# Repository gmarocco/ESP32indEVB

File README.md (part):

# ESP32-S3 Industrial Development Board — rev. 3

An ESP32-S3 development board with industrial-style I/O: an **isolated CAN bus** port, an **isolated RS-485** port, a **relay output**, two **0–30 V analog inputs**, **nine ESD-protected GPIOs**, a **3 × 3 RGB LED matrix** and a **prototyping area**. It runs from a **7–36 V DC** supply or from either of its two USB-C ports. Everything fits on a 99 × 94 mm four-layer PCB designed in KiCad 10.

## Features

- **Espressif ESP32-S3FN8**: dual-core Xtensa LX7 MCU, 2.4 GHz Wi-Fi and Bluetooth LE, 8 MB in-package flash, on-board chip antenna
- **Two USB-C ports**:
  - **debug USB**: FTDI FT230X USB-to-UART bridge on UART0
  - **native USB**: ESP32-S3 USB Serial/JTAG and USB OTG
- **Isolated CAN bus** (ESP32-S3 TWAI controller): Microchip MCP2562 transceiver, 120 Ω termination
- **Isolated RS-485**: MAX13488E half-duplex transceiver with automatic direction control, 120 Ω termination and fail-safe bias
- **Galvanic isolation** for both buses: ADuM3201 digital isolators and a Traco TEA 1-0505 isolated DC/DC converter
- **3 × 3 WS2812B RGB LED matrix** with a 3.3 V → 5 V level shifter on the data line
- **SPDT relay** (Finder 34.51, 6 A contacts) on a screw terminal block
- **Two analog inputs, 0–30 V**: resistor divider and op-amp buffer for each input
- **Nine ESD-protected GPIOs** on three 2.54 mm headers, with fused 3.3 V and 5 V outputs
- **Header for an SSD1306 I²C OLED display**
- **Wide-range supply**: 7–36 V DC input with reverse-polarity, overcurrent and transient protection, switching regulator to 5 V
- **Prototyping area** with through-hole pads and footprints for SOIC-8, MSOP-8 and SOT-23-5 parts
- **Reset, boot and user push buttons**, user LED, potentiometer on an ADC input
- **JTAG test points** and stitching vias along the board perimeter

## Block diagram

Power tree:

```mermaid
flowchart LR
    VIN["DC input 7-36 V (EXT_POWER1)"] --> PROT["F2 PTC + D4 TVS + D5 reverse-polarity diode"]
    PROT --> DCDC["TSR 1-2450 5 V regulator (PS1)"]
    DCDC -- "D6" --> OR["+5V_PRO (diode OR)"]
    USBD["Debug USB-C VBUS"] -- "D12" --> OR
    USBN["Native USB-C VBUS"] -- "D13" --> OR
    OR --> P5["+5V (F1 PTC + L5 LC filter)"]
    P5 --> LDO["NCP1117 3.3 V LDO (U1)"] --> P33["+3V3"]
    P5 --> ISO["TEA 1-0505 isolated DC/DC (PS2)"] --> P5ISO["+5V_ISO for CAN and RS-485"]
    P5 --> LEDS["WS2812B matrix, relay coil"]
    P5 -- "F3 0.5 A" --> O5["+5V_OUT (J7)"]
    P33 -- "F5 0.5 A" --> O33["+3V3_OUT (J6)"]
```

## Circuit description

The full schematic is available as a PDF file: [ESP32_ind_EVB_V3_schematic.pdf](production/ESP32_ind_EVB_V3_schematic.pdf)

| Sheet | File | Content |
|---|---|---|
| Root | `ESP32_ind_EVB_V3.kicad_sch` | Block diagram |
| gerarchico | `gerarchico.kicad_sch` | Hierarchy sheet that links the sub-sheets below |
| Power | `power.kicad_sch` | DC input, protection, 5 V switching regulator, 3.3 V LDO, fused header supplies |
| ESP32-S3 MCU | `mcu_sch.kicad_sch` | ESP32-S3, crystals, antenna, SPI flash, native USB-C, buttons, OLED header |
| bus | `bus_sch.kicad_sch` | Debug USB-C and FT230X, isolated CAN bus and RS-485, isolated DC/DC |
| GPIO | `GPIO_sch.kicad_sch` | Protected GPIO headers, analog inputs, relay, potentiometer |
| LED_MATRIX_WS2812B | `LED_MATRIX_WS2812B.kicad_sch` | 3 × 3 WS2812B matrix and level shifter |
| breadboard | `breadboard_sch.kicad_sch` | Prototyping area |

### Power supply (Power sheet)

The board has three power sources. Schottky diodes (Comchip CDBA340, 40 V / 3 A) combine them on the `+5V_PRO` node, so any of them can power the board:

| Source | Path to `+5V_PRO` |
|---|---|
| DC input `EXT_POWER1`, 7–36 V | **F2** (PTC, 1.5 A hold) → **D4** (SMBJ36CA bidirectional TVS) → **D5** (reverse-polarity diode) → **PS1** (Traco TSR 1-2450, 5 V / 1 A switching regulator) → **D6** |
| Debug USB-C (`USBC_FTDI1`) | VBUS → **D12** |
| Native USB-C (`USBC_ESP32`) | VBUS → **D13**. R40 (0 Ω, not fitted) can bypass the diode |

From `+5V_PRO`:

- **F1** (PTC, 1.5 A hold) and an LC filter (**L5**, Murata 4.7 µH, with C41 and C6) make the **+5V** rail. It feeds the LED matrix, the relay coil, the isolated DC/DC converter and the 5 V header pin.
- **U1** (onsemi NCP1117, 3.3 V LDO) makes the **+3V3** rail from +5V through **R33** (0 Ω, 0.5 W). Remove R33 to isolate the 3.3 V loads or to measure their current.
- Two ferrite beads (BLM18AG102) separate the analog supplies:
  - L1 feeds **+3.3VA** (op-amp and potentiometer).
  - L2 feeds the ESP32-S3 `VDDA` pins.
- The header supply pins are protected by 0.5 A PTC fuses and TVS diodes:
  - `+5V_OUT`: F3 and D27 (SMBJ5.0A)
  - `+3V3_OUT`: F5 and D28 (SMBJ3V3)
- **D14** shows that the 3.3 V rail is on.

> **Note:** when the board runs from USB, the +5V rail is one Schottky diode drop below VBUS.

### ESP32-S3 microcontroller (ESP32-S3 MCU sheet)

- **IC10** is an **Espressif ESP32-S3FN8** with 8 MB of in-package flash.
- **Clocks**:
  - **Y1** (Diodes FL4000157Z) is the 40 MHz main crystal, with C11 and C12 (20 pF).
  - **Y2** (Abracon ABS07AIG) is the 32.768 kHz RTC crystal on GPIO15/GPIO16, with C13 and C14 (30 pF).
- **Antenna**: **ANT1** (Walsin RFANT3216120A5T) is a 2.4 GHz chip antenna. A π matching network sits between it and the `LNA_IN` pin: L3 (2.4 nH), C48 and C49 (1.8 pF). C15 and L4 are not fitted.
- **Reset**: **S3** pulls `CHIP_PU` low. R3 and R42 (100 kΩ) pull it up, and C5 (1 µF) delays the start-up after power-on.
- **Boot and user buttons**:
  - **S4** (BOOT) is on GPIO0.
  - **S2** (user button) is on GPIO2, with a 100 kΩ pull-up (R9) and a 100 nF debounce capacitor (C20).
- **User LED**: **D15** with a 470 Ω resistor (R25). See [Known issues](#known-issues-rev-3) for its GPIO.
- **External SPI flash**: **U2** (Winbond W25Q80DV, 8 Mbit) is connected to the SPI flash bus through the 0 Ω links R2, R6, R7, R10 and R11.
- **Native USB**:
  - The USB-C receptacle **USBC_ESP32** connects to GPIO19 (D−) and GPIO20 (D+) through **IC1** (ST USBLC6-2SC6 ESD protection).
  - R12 and R14 (5.1 kΩ) pull CC1 and CC2 down, so the board is seen as a USB device.
  - The connector shield goes to GND through R13 (1 MΩ) in parallel with C21 (3.3 nF / 1 kV).
  - Header **J1** (+5V, D−, D+, GND) carries the same port, through R43/R44 (0 Ω), for a panel-mount USB connector.
- **I²C**: GPIO5 (SCL) and GPIO6 (SDA) go through 0 Ω links (R63, R64) and have 1.5 kΩ pull-ups (R67, R68). The 4-pin header **LCD1** (GND, 3V3, SCL, SDA) accepts an SSD1306 OLED module.

### USB debug port (bus sheet)

- **IC7** (FTDI **FT230XS**) is a USB-to-UART bridge connected to the ESP32-S3 UART0 through R52/R53 (0 Ω):
  - FT230X `TXD` → GPIO44 (`U0RXD`)
  - FT230X `RXD` ← GPIO43 (`U0TXD`)
- It runs from the VBUS of its own USB-C port (**USBC_FTDI1**), and its internal 3.3 V regulator sets the I/O level.
- **IC4** (USBLC6-2SC6) protects the data lines. R17 and R18 (5.1 kΩ) pull CC1 and CC2 down. The shield goes to GND through R19 (1 MΩ) in parallel with C24 (3.3 nF / 1 kV).
- **D7** and **D8** are the serial activity LEDs, driven by the FT230X `CBUS2` and `CBUS1` pins.
- Header **J4** (GND, D+, D−, VBUS) carries the same port for a panel-mount USB connector.
- The FT230X `RTS#` and `CTS#` lines are not connected, so there is no automatic reset into the bootloader. Use the BOOT button (see [Programming](#programming)).

### Isolated CAN bus and RS-485 (bus sheet)

Both buses sit in a common isolated domain:

- **PS2** (Traco TEA 1-0505) is a 1 W isolated DC/DC converter. It makes `+5V_ISO` / `GND_ISO` from +5V.
- **IC2** (CAN) and **IC3** (RS-485) are Analog Devices **ADuM3201** dual-channel digital isolators. Their MCU side runs from +3V3 and their bus side from `+5V_ISO`.
- CAN and RS-485 share the same `GND_ISO`. They are isolated from the MCU, but not from each other.

| | **CAN bus** | **RS-485** |
|---|---|---|
| MCU pins | GPIO37 TX, GPIO38 RX (TWAI controller), through R57/R56 (0 Ω) | GPIO17 TX, GPIO18 RX (UART1), through R54/R55 (0 Ω) |
| Isolator | IC2 | IC3 |
| Transceiver | **IC5**, Microchip MCP2562. `STBY` is tied low through R21, so it is always active | **IC6**, MAX13488E, half-duplex with AutoDirection: no direction pin is needed |
| Termination | R29, 120 Ω (fitted) | R28, 120 Ω (fitted) |
| Fail-safe bias | – | R22 / R23 (1 kΩ) on A / B |
| Common-mode choke | FL1, TDK ACT45B-101-2P | FL2, TDK ACT45B-101-2P |
| ESD protection | D9, Nexperia PESD2CANFD27L | D10, Nexperia PESD2CANFD27L |
| Filter capacitors | C33, C34 (100 pF to `GND_ISO`), C31 (100 pF between CANH and CANL) | C35, C36 (100 pF to `GND_ISO`) |
| Terminal block | **CAN1**: 1 CANH, 2 CANL, 3 GND_ISO | **RS1**: 1 A, 2 B, 3 GND_ISO |

> **Note:** the termination resistors are always fitted. If the board is not at one end of the bus, remove R29 (CAN) or R28 (RS-485).

### RGB LED matrix (LED_MATRIX_WS2812B sheet)

- **LED2–LED10** are nine **WS2812B** addressable RGB LEDs in a 3 × 3 matrix, powered from +5V. The colour order is GRB.
- GPIO14 drives the data line through **Q2** (Diodes DMG1012T), an N-MOSFET level shifter from 3.3 V to 5 V. R16 (2.2 kΩ) pulls the 3.3 V side up and R34 (4.7 kΩ) pulls the 5 V side up.
- Test point **DOUT3** is the data output of the last LED. Use it to extend the chain.

### Protected GPIO, analog inputs and relay (GPIO sheet)

**Protected GPIO**

Nine GPIOs have a 49.9 Ω series resistor (R30–R32, R35–R39, R41) and an ESD7351 protection diode (D1–D3, D11, D19, D22–D25). They are available on three 1 × 5 female headers, 2.54 mm pitch:

| Pin | J5 | J6 | J7 |
|---|---|---|---|
| 1 | GPIO3 | GPIO33 | GPIO36 |
| 2 | GND | GND | GND |
| 3 | GPIO4 | GPIO34 | GPIO46 ¹ |
| 4 | GND | +3V3_OUT (F5, 0.5 A) | +5V_OUT (F3, 0.5 A) |
| 5 | GPIO13 | GPIO35 | GPIO45 ¹ |

¹ The silkscreen labels of these two pins are swapped. See [Known issues](#known-issues-rev-3).

> **Note:** GPIO3, GPIO45 and GPIO46 are ESP32-S3 strapping pins. Do not drive them, or pull them up, while the board resets.

**Analog inputs**

- Terminal block **ANALOGICI1**: 1 AN2, 2 GND, 3 AN1.
- Each input has a 47 kΩ / 4.7 kΩ divider (ratio 1 : 11), followed by one half of **U3** (TI LMV358) wired as a voltage follower:
  - AN1 → GPIO12 (`ADC2_CH1`)
  - AN2 → GPIO11 (`ADC2_CH0`)
- A 30 V input gives about 2.7 V at the ADC. The input voltage is `V_in = V_adc × 11`.
- The op-amp runs from +3.3VA, so its output cannot go above the ADC supply.
- **D26** (PESD2CANFD27L) protects both inputs against ESD.

> **Note:** on the ESP32-S3 the ADC2 unit is shared with the Wi-Fi driver. Check the ESP-IDF ADC documentation if you read AN1 and AN2 while Wi-Fi is active.

**Potentiometer**

**RV1** (10 kΩ, Bourns 3314G) is connected between GND and +3.3VA. Its wiper goes to GPIO10 (`ADC1_CH9`), which is useful to test the ADC.

**Relay**

- **K1** (Finder 34.51) is an SPDT relay with a 5 V coil, powered from +5V.
- GPIO21 drives it through R47 (0 Ω) and **Q1** (Diodes DRDC3105F), a relay driver with built-in bias resistors and flyback diode.
- The contacts are on terminal block **RELE1**: 1 NO, 2 COM, 3 NC.

### Prototyping area (breadboard sheet)

The area marked *SEZIONE ESPERIMENTI* on the silkscreen has through-hole pads on a grid, with GND, +5V and +3V3 pads at the edges. It also has three SMD footprints with every pin brought out to a pad:

- **IC8**: SOIC-8 (NE555 in the BOM)
- **IC9**: MSOP-8 (NE555 in the BOM)
- **U4**: SOT-23-5 (NCP718 LDO in the BOM)

### GPIO map

| GPIO | Function |
|---|---|
| GPIO0 | BOOT button S4 |
| GPIO1 | Test pad TP72 |
| GPIO2 | User button S2 |
| GPIO3, GPIO4, GPIO13 | Protected GPIO, header J5 |
| GPIO5 / GPIO6 | I²C SCL / SDA (OLED header LCD1) |
| GPIO9 | User LED D15 (rev. 3 PCB, see [Known issues](#known-issues-rev-3)) |
| GPIO10 | Potentiometer RV1 (`ADC1_CH9`) |
| GPIO11 / GPIO12 | Analog inputs AN2 / AN1 (`ADC2_CH0` / `ADC2_CH1`) |
| GPIO14 | WS2812B LED matrix data |
| GPIO15 / GPIO16 | 32.768 kHz crystal |
| GPIO17 / GPIO18 | RS-485 TX / RX (UART1) |
| GPIO19 / GPIO20 | Native USB D− / D+ |
| GPIO21 | Relay K1 |
| GPIO26 | Test point SPICS1 |
| GPIO33, GPIO34, GPIO35 | Protected GPIO, header J6 |
| GPIO36, GPIO45, GPIO46 | Protected GPIO, header J7 |
| GPIO37 / GPIO38 | CAN TX / RX (TWAI) |
| GPIO39–GPIO42 | JTAG test points MTCK, MTDO, MTDI, MTMS |
| GPIO43 / GPIO44 | UART0 TX / RX to the FT230X (debug USB) |
| GPIO47 / GPIO48 | Test points K_N1 / K_P1 |

### Indicators, buttons and test points

| Ref | Function |
|---|---|
| D14 | 3.3 V rail on |
| D15 | User LED |
| D7, D8 | FT230X serial activity |
| S2 | User button (GPIO2) |
| S3 | RESET (`CHIP_PU`) |
| S4 | BOOT (GPIO0) |
| MTCK1, MTDO1, MTDI1, MTMS1 | JTAG |
| DOUT3 | Data output of the LED matrix |
| SPICS1, K_P1, K_N1, TP72 | GPIO26, GPIO48, GPIO47, GPIO1 |

## Main components

| Ref | Part | Function |
|---|---|---|
| IC10 | Espressif ESP32-S3FN8 | Dual-core MCU, Wi-Fi + Bluetooth LE, 8 MB flash |
| Y1 | Diodes FL4000157Z | 40 MHz crystal |
| Y2 | Abracon ABS07AIG-32.768KHZ | 32.768 kHz RTC crystal |
| ANT1 | Walsin RFANT3216120A5T | 2.4 GHz chip antenna |
| U2 | Winbond W25Q80DVSNIG | 8 Mbit SPI NOR flash |
| IC7 | FTDI FT230XS-R | USB ⇄ UART bridge (debug port) |
| IC1, IC4 | ST USBLC6-2SC6 | ESD protection for the USB data lines |
| IC5 | Microchip MCP2562-E/SN | CAN transceiver |
| IC6 | Analog Devices MAX13488EESA+ | RS-485 transceiver with AutoDirection |
| IC2, IC3 | Analog Devices ADuM3201ARZ | Dual-channel digital isolators |
| PS2 | Traco TEA 1-0505 | 1 W isolated DC/DC converter, 5 V → 5 V |
| PS1 | Traco TSR 1-2450 | 5 V / 1 A switching regulator |
| U1 | onsemi NCP1117, 3.3 V, TO-252 | 3.3 V LDO regulator |
| U3 | TI LMV358IDR | Dual op-amp, analog input buffers |
| Q1 | Diodes DRDC3105F-7 | Relay driver |
| K1 | Finder 34.51 | SPDT relay, 5 V coil, 6 A contacts |
| Q2 | Diodes DMG1012T | N-MOSFET, LED data level shifter |
| LED2–LED10 | WS2812B | Addressable RGB LEDs |
| FL1, FL2 | TDK ACT45B-101-2P-TL003 | Common-mode chokes for CAN and RS-485 |
| D9, D10, D26 | Nexperia PESD2CANFD27L | ESD protection for CAN, RS-485 and analog inputs |
| D1–D3, D11, D19, D22–D25 | onsemi ESD7351HT1G | ESD protection for the GPIOs |
| D4 | SMBJ36CA | Bidirectional TVS on the DC input |
| D27, D28 | SMBJ5.0A, SMBJ3V3 | TVS on the header supply pins |
| D5, D6, D12, D13 | Comchip CDBA340-HF | Schottky diodes: reverse polarity and OR-ing |
| F1, F2 | Littelfuse 1812L150/24MR | PTC resettable fuses, 1.5 A hold |
| F3, F5 | Littelfuse 1206L050/15YR | PTC resettable fuses, 0.5 A hold |
| L5 | Murata DFE322512F-4R7M | 4.7 µH inductor, +5V filter |
| S2, S3, S4 | Panasonic EVQ-PE104K | Push buttons |
| USBC_ESP32, USBC_FTDI1 | CUI UJ31-CH-G2-SMT-TR | USB Type-C receptacles |
| CAN1, RS1, ANALOGICI1, RELE1 | TE 282837-3 | 3-pole terminal blocks, 5.08 mm |
| EXT_POWER1 | TE 282837-2 | 2-pole terminal block, 5.08 mm |

The complete bill of materials is in [`bom.csv`](production/bom.csv). An interactive BOM is in [`ESP32-S3 ind_EVB rV3ibom.html`](production/ESP32-S3%20ind_EVB%20rV3ibom.html): download it and open it in a browser.

## PCB

| Parameter | Value |
|---|---|
| Layers | 4 (F.Cu, In1.Cu GND plane, In2.Cu GND plane, B.Cu) |
| Board size | 99.3 × 94.2 mm |
| Mounting | 2 × M3 holes (H1, H2) |
| Supply | 7–36 V DC on a terminal block, or 5 V from either USB-C port |
| Connectors | 2 × USB-C, 4 × 3-pole and 1 × 2-pole 5.08 mm terminal blocks, 3 × 1×5 GPIO headers, 1 × 4-pin OLED header, 2 × 4-pin USB headers |
| EDA tool | KiCad 10.0 |

## Repository contents

| Path | Description |
|---|---|
| `hardware/ESP32_ind_EVB_V3.kicad_pro` | KiCad 10 project file |
| `hardware/ESP32_ind_EVB_V3.kicad_sch` and sub-sheets | Hierarchical schematic (see the sheet table above) |
| `hardware/ESP32_ind_EVB_V3.kicad_pcb` | PCB layout |
| `hardware/lib/` | Project libraries: symbols (`ESP32indEVB.kicad_sym`), footprints (`ESP32indEVB.pretty`) and 3D models (`3dmodels`) |
| `production/gerber ESP32_ind_EVB_V3.zip` | Gerber manufacturing files |
| `production/bom.csv`, `designators.csv`, `positions.csv` | Bill of materials and pick-and-place files |
| `production/netlist.ipc` | IPC-D-356 netlist |
| `production/ESP32_ind_EVB_V3_schematic.pdf` | Schematic |
| `production/ESP32-S3 ind_EVB rV3ibom.html` | Interactive BOM |
| `firmware/` | Arduino examples |
| `docs/` | Pictures used in this README |

The project is self-contained: the libraries in `hardware/lib/` are linked through the project library tables, so you do not need to install any external library.

## Programming

The examples use the Arduino IDE with the **esp32** board package by Espressif Systems.

1. In **Tools**, select these settings (see the [screenshot](firmware/board%20configuration.png)):
   - Board: **ESP32-S3-USB-OTG**
   - USB Mode: **USB-OTG**
   - Upload Mode: **UART0 / Hardware CDC**
   - Port: the COM port of the board
2. Put the ESP32-S3 in download mode. Press and hold **BOOT** (S4) before you plug in the USB cable, and release it a few seconds after plugging it in. If the board is already powered, hold BOOT, press and release RESET (S3), then release BOOT.
3. Upload the sketch, then press **RESET** to run it.

| Example | Description |
|---|---|
| [`TWAItransmit`](firmware/TWAItransmit) | Sends CAN frames at 500 kbit/s (TWAI, TX GPIO37, RX GPIO38) |
| [`TWAIreceive`](firmware/TWAIreceive) | Receives CAN frames at 500 kbit/s in listen-only mode |
| [`RS485_TX`](firmware/RS485_TX) | Sends data on RS-485 at 9600 baud (UART on GPIO17/GPIO18) |
| [`rs485_RX`](firmware/rs485_RX) | Receives data on RS-485 at 9600 baud |
| [`random_generator_LEDS`](firmware/random_generator_LEDS) | Fades the LED matrix through random colours (FastLED, GPIO14) |
| [`fastLED_webserver`](firmware/fastLED_webserver) | Web page that sets the colour and brightness of the LED matrix over Wi-Fi. Enter your network name and password in the sketch |

## Known issues (rev. 3)

- **GPIO45 / GPIO46 labels swapped**: the schematic net labels, and so the silkscreen of header J7, are swapped. Pin 3, labelled GP45, is connected to **GPIO46**. Pin 5, labelled GP46, is connected to **GPIO45**. The tables in this README show the real GPIO numbers.
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
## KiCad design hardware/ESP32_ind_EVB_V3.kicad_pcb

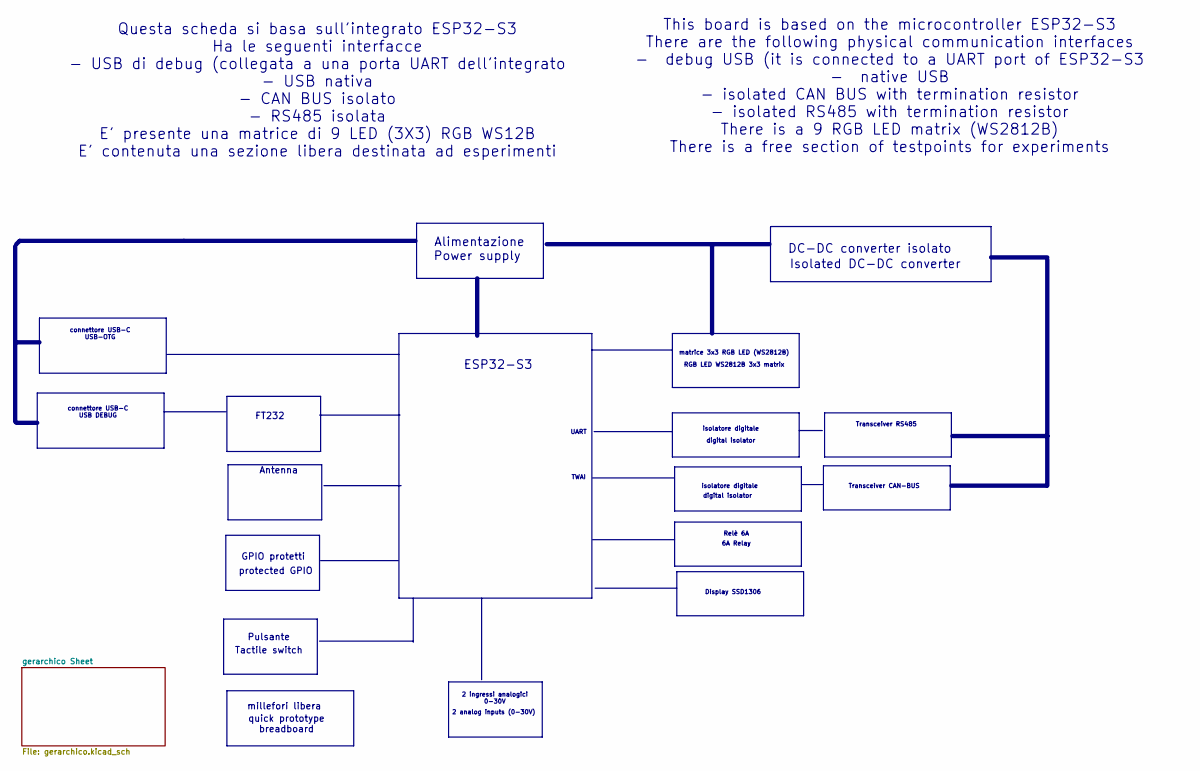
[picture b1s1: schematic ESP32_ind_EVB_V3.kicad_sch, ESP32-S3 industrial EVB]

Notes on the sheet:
TWAI
FT232
isolatore digitale
Transceiver RS485
matrice 3x3 RGB LED (WS2812B)
This board is based on the microcontroller ESP32-S3 There are the following physical communication interfaces - debug USB (it is connected to a UART port of ESP32-S3 - native USB - isolated CAN BUS with termination resistor - isolated RS485 with termination resistor There is a 9 RGB LED matrix (WS2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
Alimentazione
GPIO protetti
ESP32-S3
Transceiver CAN-BUS
millefori libera
Power supply
quick prototype breadboard
Questa scheda si basa sull'integrato ESP32-S3 Ha le seguenti interfacce - USB di debug (collegata a una porta UART dell'integrato - USB nativa - CAN BUS isolato - RS485 isolata E' presente una matrice di 9 LED (3X3) RGB WS12B E' contenuta una sezione libera destinata ad esperimenti
6A Relay
digital isolator
Pulsante
connettore USB-C USB-OTG
DC-DC converter isolato
Display SSD1306
Isolated DC-DC converter
2 analog inputs (0-30V)
protected GPIO
RGB LED WS2812B 3x3 matrix
Antenna
Relè 6A
2 ingressi analogici 0-30V
connettore USB-C USB DEBUG
Tactile switch
UART

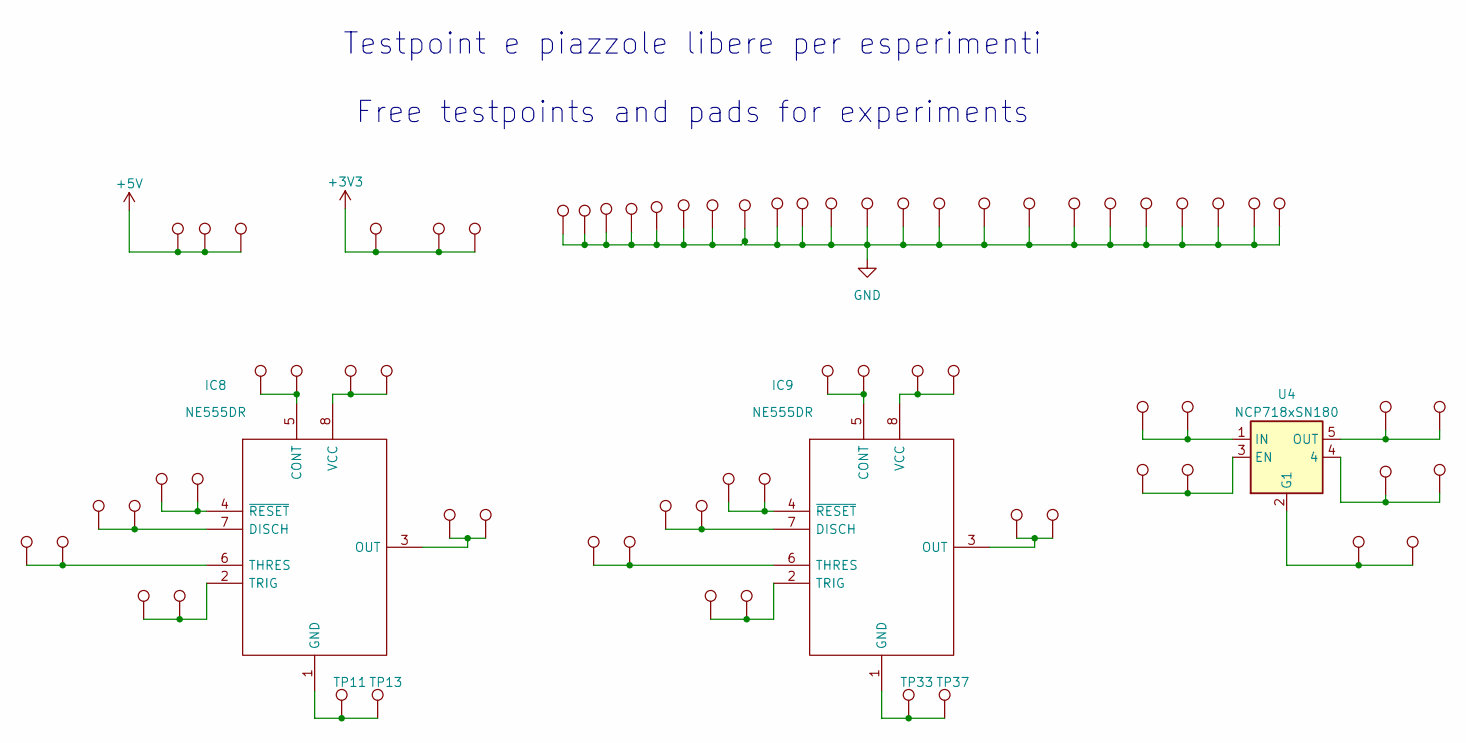
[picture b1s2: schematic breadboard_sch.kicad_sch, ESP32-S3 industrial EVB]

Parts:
IC8: NE555DR; SO-8_3.9x4.9mm_P1.27mm; Manufacturer_Part_Number NE555DR; Mouser Part Number 595-NE555DR
IC9: NE555DR; MSOP-8_3x3mm_P0.65mm; Manufacturer_Part_Number NE555DR; Mouser Part Number 595-NE555DR
TP1, TP2, TP3, TP4, TP5, TP6, TP7, TP8, TP9, TP10, TP11, TP12, TP13, TP14, TP15, TP16, TP17, TP18, TP19, TP20, TP21, TP22, TP23, TP24, TP25, TP26, TP27, TP28, TP29, TP30, TP31, TP32, TP33, TP34, TP35, TP36, TP37, TP38, TP39, TP40, TP41, TP42, TP43, TP44, TP45, TP46, TP47, TP48, TP49, TP50, TP51, TP52, TP53, TP54, TP55, TP56, TP57, TP58, TP59, TP60, TP61, TP62, TP63, TP64, TP65, TP66, TP67, TP68, TP69, TP70, TP71: TestPoint; TestPoint_Pad_through hole 1.5mm
U4: NCP718xSN180; SOT-23-5

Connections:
+3V3: TP25.1 (1_1), TP29.1 (1_1), TP30.1 (1_1); also elsewhere on the board
+5V: TP17.1 (1_1), TP18.1 (1_1), TP19.1 (1_1); also elsewhere on the board
GND: TP34.1 (1_1), TP36.1 (1_1), TP38.1 (1_1), TP40.1 (1_1), TP41.1 (1_1), TP43.1 (1_1), TP45.1 (1_1), TP46.1 (1_1), TP47.1 (1_1), TP50.1 (1_1), TP51.1 (1_1), TP54.1 (1_1), TP55.1 (1_1), TP56.1 (1_1), TP57.1 (1_1), TP59.1 (1_1), TP63.1 (1_1), TP66.1 (1_1), TP67.1 (1_1), TP68.1 (1_1), TP69.1 (1_1), TP70.1 (1_1), TP71.1 (1_1); also elsewhere on the board
unnamed: IC8.5 (CONT), TP9.1 (1_1), TP10.1 (1_1)
unnamed: IC8.7 (DISCH), TP3.1 (1_1), TP4.1 (1_1)
unnamed: IC8.1 (GND), TP11.1 (1_1), TP13.1 (1_1)
unnamed: IC8.3 (OUT), TP15.1 (1_1), TP16.1 (1_1)
unnamed: IC8.6 (THRES), TP1.1 (1_1), TP2.1 (1_1)
unnamed: IC8.2 (TRIG), TP5.1 (1_1), TP7.1 (1_1)
unnamed: IC8.8 (VCC), TP12.1 (1_1), TP14.1 (1_1)
unnamed: IC8.4 (~RESET), TP6.1 (1_1), TP8.1 (1_1)
unnamed: IC9.5 (CONT), TP31.1 (1_1), TP32.1 (1_1)
unnamed: IC9.7 (DISCH), TP22.1 (1_1), TP23.1 (1_1)
unnamed: IC9.1 (GND), TP33.1 (1_1), TP37.1 (1_1)
unnamed: IC9.3 (OUT), TP42.1 (1_1), TP44.1 (1_1)
unnamed: IC9.6 (THRES), TP20.1 (1_1), TP21.1 (1_1)
unnamed: IC9.2 (TRIG), TP24.1 (1_1), TP27.1 (1_1)
unnamed: IC9.8 (VCC), TP35.1 (1_1), TP39.1 (1_1)
unnamed: IC9.4 (~RESET), TP26.1 (1_1), TP28.1 (1_1)
unnamed: TP61.1 (1_1), TP65.1 (1_1), U4.4
unnamed: TP49.1 (1_1), TP53.1 (1_1), U4.3 (EN)
unnamed: TP58.1 (1_1), TP62.1 (1_1), U4.2 (G1)
unnamed: TP48.1 (1_1), TP52.1 (1_1), U4.1 (IN)
unnamed: TP60.1 (1_1), TP64.1 (1_1), U4.5 (OUT)

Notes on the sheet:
Testpoint e piazzole libere per esperimenti Free testpoints and pads for experiments

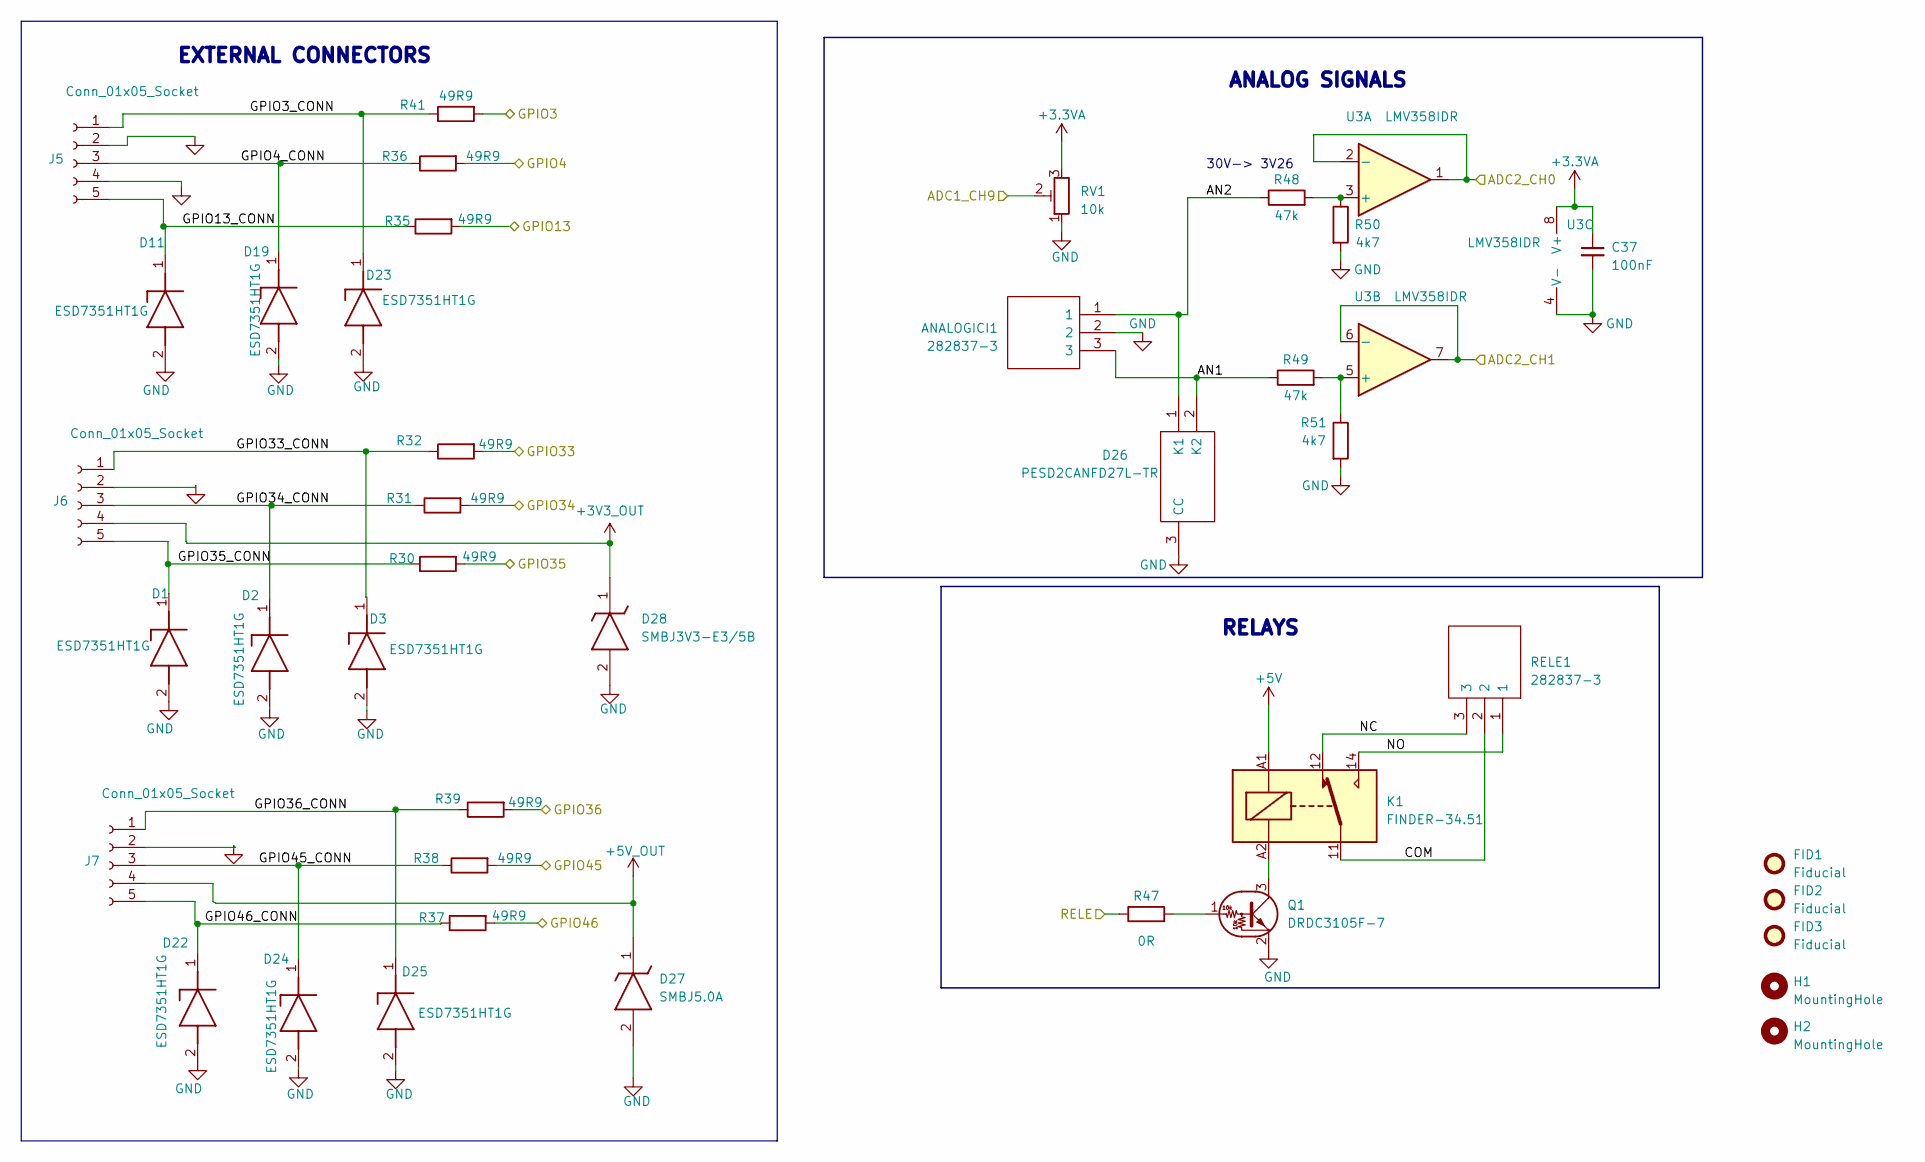
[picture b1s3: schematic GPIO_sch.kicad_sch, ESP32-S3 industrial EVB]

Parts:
ANALOGICI1: 282837-3; TerminalBlock_bornier-3_P5.08mm; Mouser Part Number 490-TB006-508-03BE
C37: 100nF; C_0603_1608Metric_Pad1.08x0.95mm_HandSolder
D1, D2, D3, D11, D19, D22, D23, D24, D25: ESD7351HT1G; SOD-323; Mouser Part Number 771-PESD3V3U1UB-T/R
D26: PESD2CANFD27L-TR; SOT-23-3; Mouser Part Number 771-PESD2CANFD24L-UX
D27: SMBJ5.0A; DIOM5436X244N; Mouser Part Number 78-SMBJ5.0A
D28: SMBJ3V3-E3/5B; DIOM5436X244N; Mouser Part Number 78-SMBJ5.0A
FID1, FID2, FID3: Fiducial; Fiducial_1.5mm_Mask3mm
H1, H2: MountingHole; MountingHole_3.2mm_M3
J5, J6, J7: Conn_01x05_Socket; PinSocket_1x05_P2.54mm_Vertical
K1: FINDER-34.51; Relay_SPDT_Finder_34.51_Vertical
Q1: DRDC3105F-7; SOT-23-3
R30, R31, R32, R35, R36, R37, R38, R39, R41: 49R9; R_0805_2012Metric_Pad1.20x1.40mm_HandSolder
R47: 0R; R_0603_1608Metric_Pad0.98x0.95mm_HandSolder
R48, R49: 47k; R_0603_1608Metric_Pad0.98x0.95mm_HandSolder
R50, R51: 4k7; R_0603_1608Metric_Pad0.98x0.95mm_HandSolder
RELE1: 282837-3; TerminalBlock_bornier-3_P5.08mm; Mouser Part Number 490-TB006-508-03BE
RV1: 10k; Potentiometer_Bourns_3314G_Vertical
U3: LMV358IDR; SO-8_3.9x4.9mm_P1.27mm

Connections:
+3.3VA: C37.1, RV1.3, U3.8 (V+); also elsewhere on the board
+3V3_OUT: D28.1 (K), J6.4; also elsewhere on the board
+5V: K1.A1; also elsewhere on the board
+5V_OUT: D27.1 (K), J7.4; also elsewhere on the board
/gerarchico Sheet/ESP32-S3 MCU/ADC1_CH9: RV1.2; also elsewhere on the board
/gerarchico Sheet/ESP32-S3 MCU/ADC2_CH0: U3.1, U3.2 (-); also elsewhere on the board
/gerarchico Sheet/ESP32-S3 MCU/ADC2_CH1: U3.6 (-), U3.7; also elsewhere on the board
/gerarchico Sheet/ESP32-S3 MCU/GPIO3: R41.2; also elsewhere on the board
/gerarchico Sheet/ESP32-S3 MCU/GPIO4: R36.2; also elsewhere on the board
/gerarchico Sheet/ESP32-S3 MCU/GPIO13: R35.2; also elsewhere on the board
/gerarchico Sheet/ESP32-S3 MCU/GPIO33: R32.2; also elsewhere on the board
/gerarchico Sheet/ESP32-S3 MCU/GPIO34: R31.2; also elsewhere on the board
/gerarchico Sheet/ESP32-S3 MCU/GPIO35: R30.2; also elsewhere on the board
/gerarchico Sheet/ESP32-S3 MCU/GPIO36: R39.2; also elsewhere on the board
/gerarchico Sheet/ESP32-S3 MCU/GPIO45: R38.2; also elsewhere on the board
/gerarchico Sheet/ESP32-S3 MCU/GPIO46: R37.2; also elsewhere on the board
/gerarchico Sheet/ESP32-S3 MCU/RELE: R47.1; also elsewhere on the board
/gerarchico Sheet/GPIO/AN1: ANALOGICI1.3, D26.2 (K2), R49.1
/gerarchico Sheet/GPIO/AN2: ANALOGICI1.1, D26.1 (K1), R48.1
/gerarchico Sheet/GPIO/COM: K1.11, RELE1.2
/gerarchico Sheet/GPIO/GPIO3_CONN: D23.1 (K), J5.1, R41.1
/gerarchico Sheet/GPIO/GPIO4_CONN: D19.1 (K), J5.3, R36.1
/gerarchico Sheet/GPIO/GPIO13_CONN: D11.1 (K), J5.5, R35.1
/gerarchico Sheet/GPIO/GPIO33_CONN: D3.1 (K), J6.1, R32.1
/gerarchico Sheet/GPIO/GPIO34_CONN: D2.1 (K), J6.3, R31.1
/gerarchico Sheet/GPIO/GPIO35_CONN: D1.1 (K), J6.5, R30.1
/gerarchico Sheet/GPIO/GPIO36_CONN: D25.1 (K), J7.1, R39.1
/gerarchico Sheet/GPIO/GPIO45_CONN: D24.1 (K), J7.3, R38.1
/gerarchico Sheet/GPIO/GPIO46_CONN: D22.1 (K), J7.5, R37.1
/gerarchico Sheet/GPIO/NC: K1.12, RELE1.3
/gerarchico Sheet/GPIO/NO: K1.14, RELE1.1
GND: ANALOGICI1.2, C37.2, D1.2 (A), D2.2 (A), D3.2 (A), D11.2 (A), D19.2 (A), D22.2 (A), D23.2 (A), D24.2 (A), D25.2 (A), D26.3 (CC), D27.2 (A), D28.2 (A), J5.2, J5.4, J6.2, J7.2, Q1.2 (E), R50.2, R51.2, RV1.1, U3.4 (V-); also elsewhere on the board
unnamed: Q1.1 (B), R47.2
unnamed: K1.A2, Q1.3 (C)
unnamed: R48.2, R50.1, U3.3 (+)
unnamed: R49.2, R51.1, U3.5 (+)

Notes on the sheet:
30V-> 3V26
ANALOG SIGNALS
RELAYS
EXTERNAL CONNECTORS

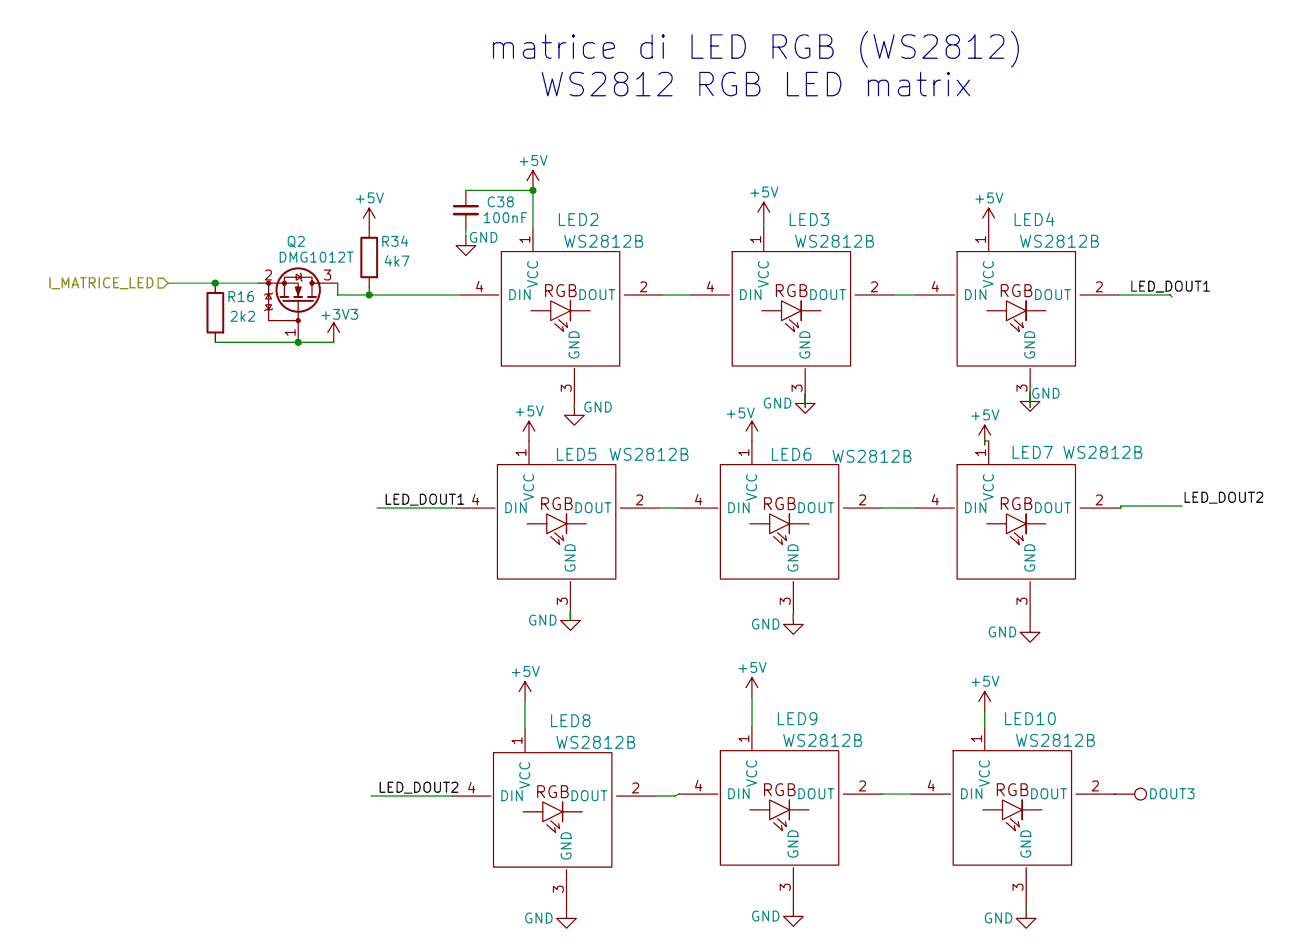
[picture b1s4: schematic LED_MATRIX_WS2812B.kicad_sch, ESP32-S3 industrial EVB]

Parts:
C38: 100nF; C_0603_1608Metric_Pad1.08x0.95mm_HandSolder
DOUT3: TestPoint; TestPoint_THTPad_D1.0mm_Drill0.5mm
LED2, LED3, LED4, LED5, LED6, LED7, LED8, LED9, LED10: WS2812B
Q2: DMG1012T; SOT-523
R16: 2k2; R_0603_1608Metric_Pad0.98x0.95mm_HandSolder
R34: 4k7; R_0603_1608Metric_Pad0.98x0.95mm_HandSolder

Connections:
+3V3: Q2.1 (G), R16.2; also elsewhere on the board
+5V: C38.1, LED2.1 (VCC), LED3.1 (VCC), LED4.1 (VCC), LED5.1 (VCC), LED6.1 (VCC), LED7.1 (VCC), LED8.1 (VCC), LED9.1 (VCC), LED10.1 (VCC), R34.1; also elsewhere on the board
/gerarchico Sheet/ESP32-S3 MCU/I_MATRICE_LED: Q2.2 (S), R16.1; also elsewhere on the board
/gerarchico Sheet/LED_MATRIX_WS2812B/LED_DOUT1: LED4.2 (DOUT), LED5.4 (DIN)
/gerarchico Sheet/LED_MATRIX_WS2812B/LED_DOUT2: LED7.2 (DOUT), LED8.4 (DIN)
GND: C38.2, LED2.3 (GND), LED3.3 (GND), LED4.3 (GND), LED5.3 (GND), LED6.3 (GND), LED7.3 (GND), LED8.3 (GND), LED9.3 (GND), LED10.3 (GND); also elsewhere on the board
unnamed: LED2.4 (DIN), Q2.3 (D), R34.2
unnamed: LED2.2 (DOUT), LED3.4 (DIN)
unnamed: LED3.2 (DOUT), LED4.4 (DIN)
unnamed: LED5.2 (DOUT), LED6.4 (DIN)
unnamed: LED6.2 (DOUT), LED7.4 (DIN)
unnamed: LED8.2 (DOUT), LED9.4 (DIN)
unnamed: LED9.2 (DOUT), LED10.4 (DIN)
unnamed: DOUT3.1 (1_1), LED10.2 (DOUT)

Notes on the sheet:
matrice di LED RGB (WS2812) WS2812 RGB LED matrix

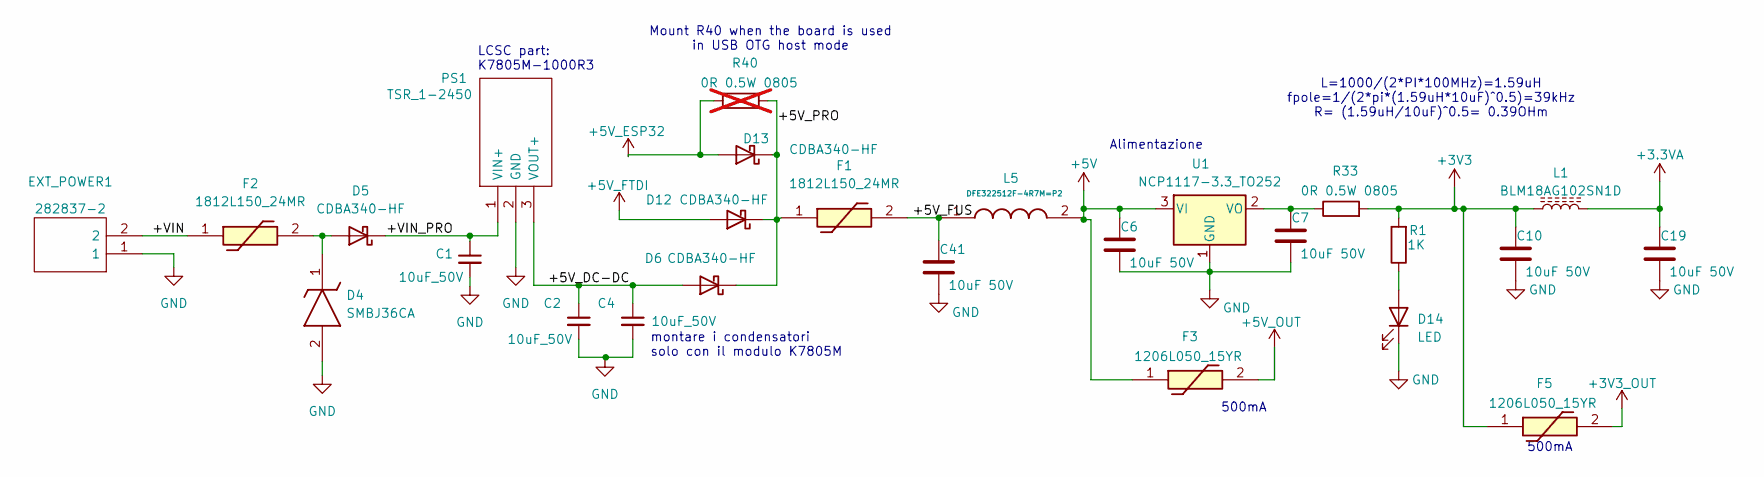
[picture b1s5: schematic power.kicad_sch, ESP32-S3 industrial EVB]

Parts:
C1, C2, C4: 10uF_50V; C_1206_3216Metric_Pad1.33x1.80mm_HandSolder
C6, C7, C10, C19, C41: 10uF 50V; C_1206_3216Metric_Pad1.33x1.80mm_HandSolder
D4: SMBJ36CA; DIOM5436X261N; Mouser Part Number SMBJ36CA
D5, D6, D12, D13: CDBA340-HF; SMA
D14: LED; LED_0603_1608Metric_Pad1.05x0.95mm_HandSolder
EXT_POWER1: 282837-2; 2828372; Mouser Part Number 571-2828372
F1, F2: 1812L150_24MR; 1812L010DR; Mouser Part Number 576-1812L150/24MR
F3, F5: 1206L050_15YR; 1206L05015YR; Mouser Part Number 576-1206L050/15YR
L1: BLM18AG102SN1D; L_0603_1608Metric_Pad1.05x0.95mm_HandSolder
L5: DFE322512F-4R7M=P2; 1277ASH100MP2; Mouser Part Number 81-DFE322512F-4R7MP2
PS1: TSR_1-2450; Converter_DCDC_TRACO_TSR-1_THT; Mouser Part Number 495-TSR-1-2450
R1: 1K; R_0603_1608Metric_Pad0.98x0.95mm_HandSolder
R33: 0R 0.5W 0805; R_0805_2012Metric_Pad1.20x1.40mm_HandSolder
R40: 0R 0.5W 0805; R_0805_2012Metric_Pad1.20x1.40mm_HandSolder; not fitted
U1: NCP1117-3.3_TO252; TO-252-2

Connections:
+3.3VA: C19.1, L1.2; also elsewhere on the board
+3V3: C10.1, F5.1, L1.1, R1.2, R33.2; also elsewhere on the board
+3V3_OUT: F5.2; also elsewhere on the board
+5V: C6.1, F3.1, L5.2, U1.3 (VI); also elsewhere on the board
+5V_ESP32: D13.2 (A), R40.1; also elsewhere on the board
+5V_FTDI: D12.2 (A); also elsewhere on the board
+5V_OUT: F3.2; also elsewhere on the board
/gerarchico Sheet/Power/+5V_DC-DC: C2.1, C4.1, D6.2 (A), PS1.3 (VOUT+)
/gerarchico Sheet/Power/+5V_FUS: C41.1, F1.2, L5.1
/gerarchico Sheet/Power/+5V_PRO: D6.1 (K), D12.1 (K), D13.1 (K), F1.1, R40.2
/gerarchico Sheet/Power/+VIN: EXT_POWER1.2, F2.1
/gerarchico Sheet/Power/+VIN_PRO: C1.1, D5.1 (K), PS1.1 (VIN+)
GND: C1.2, C2.2, C4.2, C6.2, C7.2, C10.2, C19.2, C41.2, D4.2 (A), D14.1 (K), EXT_POWER1.1, PS1.2 (GND), U1.1 (GND); also elsewhere on the board
unnamed: D4.1 (K), D5.2 (A), F2.2
unnamed: D14.2 (A), R1.1
unnamed: C7.1, R33.1, U1.2 (VO)

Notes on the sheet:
500mA
L=1000/(2*PI*100MHz)=1.59uH fpole=1/(2*pi*(1.59uH*10uF)^0.5)=39kHz R= (1.59uH/10uF)^0.5= 0.39OHm
LCSC part: K7805M-1000R3
Mount R40 when the board is used in USB OTG host mode
montare i condensatori solo con il modulo K7805M
Alimentazione

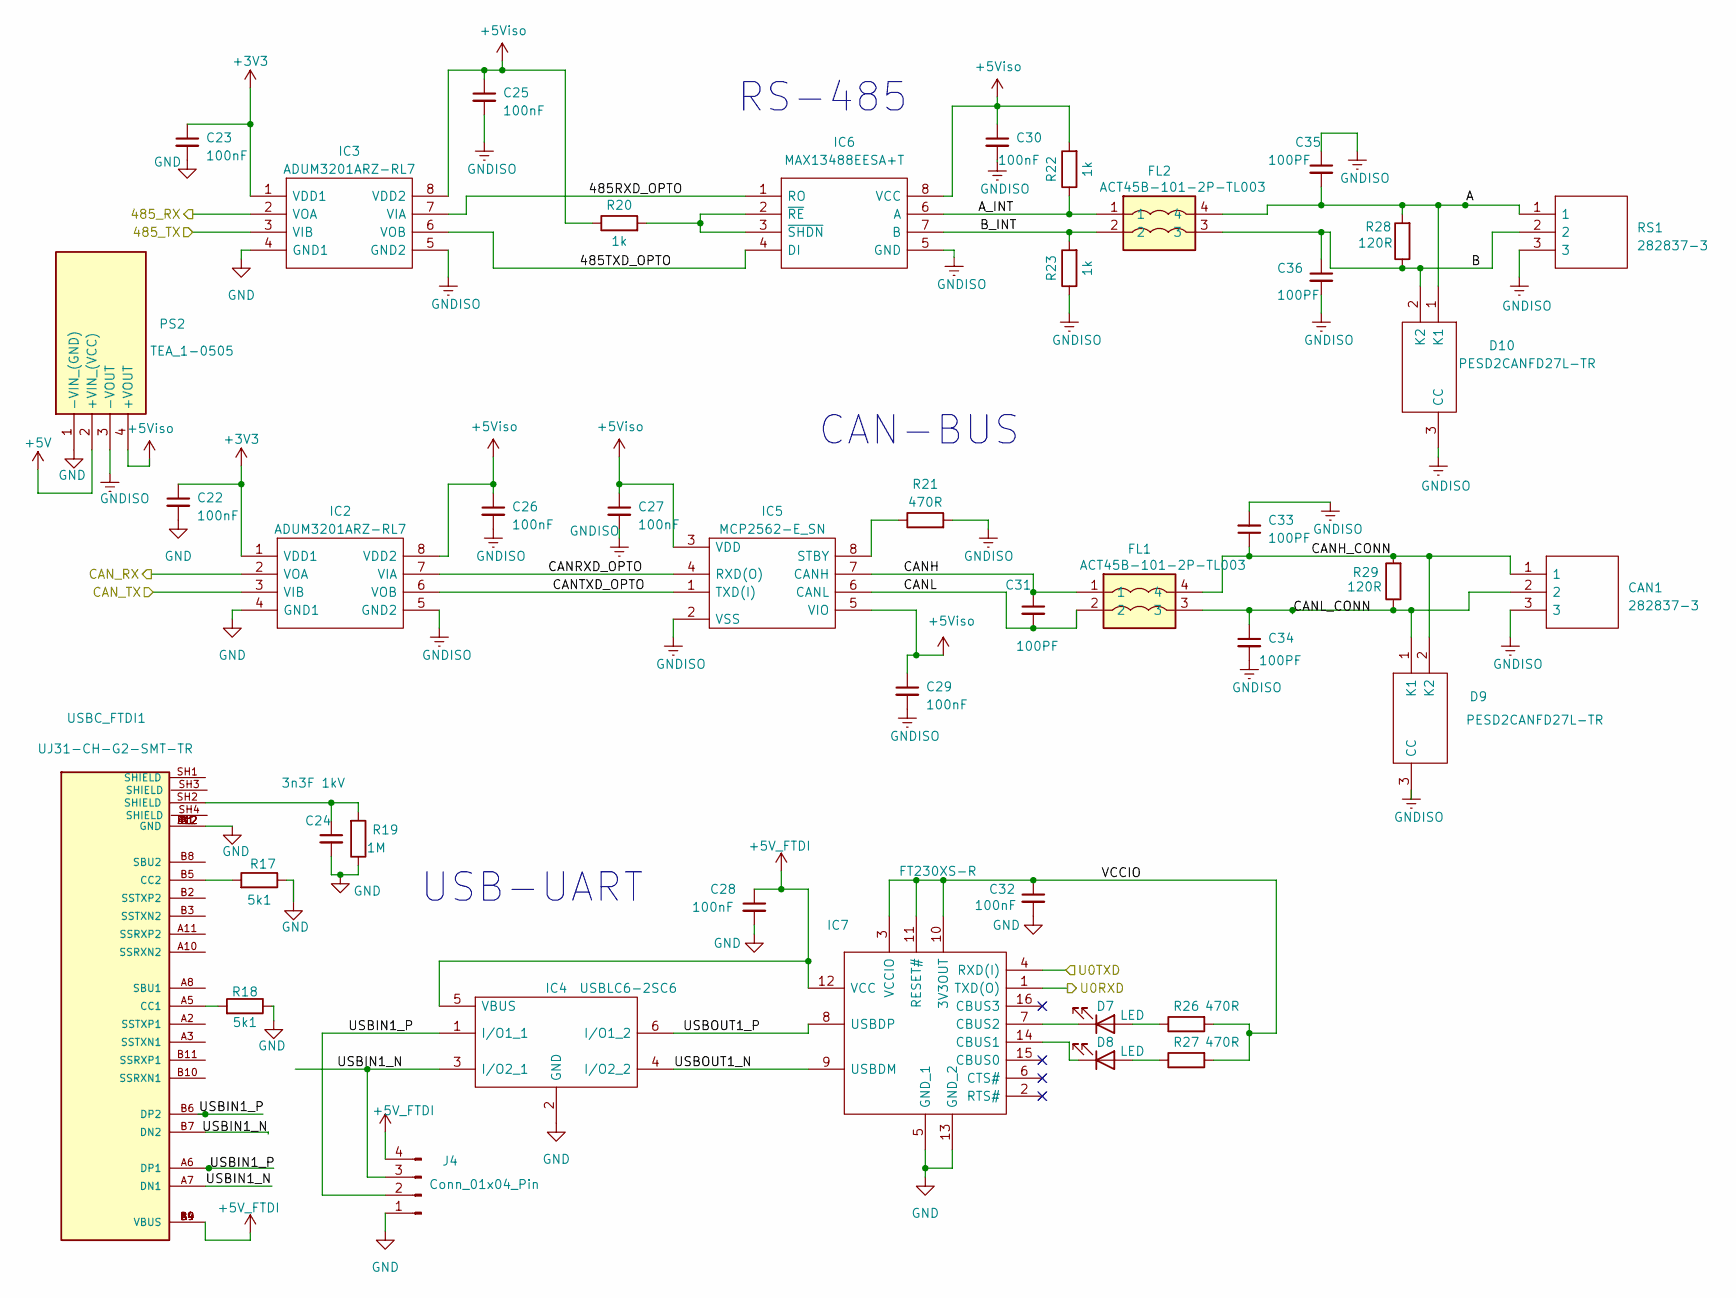
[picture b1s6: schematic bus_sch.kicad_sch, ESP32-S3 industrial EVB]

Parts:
C22, C23, C25, C26, C27, C28, C29, C30, C32: 100nF; C_0603_1608Metric_Pad1.08x0.95mm_HandSolder
C24: 3n3F 1kV; C_1206_3216Metric_Pad1.33x1.80mm_HandSolder
C31, C33, C34, C35, C36: 100PF; C_0603_1608Metric_Pad1.08x0.95mm_HandSolder
CAN1: 282837-3; TerminalBlock_bornier-3_P5.08mm; Mouser Part Number 490-TB006-508-03BE
D7, D8: LED; LED_0603_1608Metric_Pad1.05x0.95mm_HandSolder
D9, D10: PESD2CANFD27L-TR; SOT-23-3; Mouser Part Number 771-PESD2CANFD24L-UX
FL1, FL2: ACT45B-101-2P-TL003; ACT45B1012PTL003; Mouser Part Number 810-ACT1210D1012PTL0
IC2, IC3: ADUM3201ARZ-RL7; SO-8_3.9x4.9mm_P1.27mm; Mouser Part Number 584-ADUM3201ARZ-R7
IC4: USBLC6-2SC6; SOT23-6; Mouser Part Number 511-USBLC6-2SC6
IC5: MCP2562-E_SN; SO-8_3.9x4.9mm_P1.27mm; Mouser Part Number 579-MCP2562-E/SN
IC6: MAX13488EESA+T; SO-8_3.9x4.9mm_P1.27mm; Mouser Part Number 700-MAX13488EESAT
IC7: FT230XS-R; TSSOP-16_4.4x5mm_P0.65mm; Mouser Part Number 895-FT230XS-R
J4: Conn_01x04_Pin; PinHeader_1x04_P2.54mm_Vertical
PS2: TEA_1-0505; TEA10505; Mouser Part Number 495-TEA1-0505
R17, R18: 5k1; R_0603_1608Metric_Pad0.98x0.95mm_HandSolder
R19: 1M; R_0603_1608Metric_Pad0.98x0.95mm_HandSolder
R20, R22, R23: 1k; R_0603_1608Metric_Pad0.98x0.95mm_HandSolder
R21, R26, R27: 470R; R_0603_1608Metric_Pad0.98x0.95mm_HandSolder
R28, R29: 120R; R_0805_2012Metric_Pad1.20x1.40mm_HandSolder
RS1: 282837-3; TerminalBlock_bornier-3_P5.08mm; Mouser Part Number 490-TB006-508-03BE
USBC_FTDI1: UJ31-CH-G2-SMT-TR; UJ31CHG2SMTTR; PART_REV 1.01

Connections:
+3V3: C22.1, C23.1, IC2.1 (VDD1), IC3.1 (VDD1); also elsewhere on the board
+5V: PS2.2 (+VIN_(VCC)); also elsewhere on the board
+5V_FTDI: C28.1, IC4.5 (VBUS), IC7.12 (VCC), J4.4, USBC_FTDI1.A4 (VBUS), USBC_FTDI1.A9 (VBUS), USBC_FTDI1.B4 (VBUS), USBC_FTDI1.B9 (VBUS); also elsewhere on the board
+5Viso: C25.1, C26.1, C27.1, C29.1, C30.1, IC2.8 (VDD2), IC3.8 (VDD2), IC5.3 (VDD), IC5.5 (VIO), IC6.8 (VCC), PS2.4 (+VOUT), R20.1, R22.2
/gerarchico Sheet/ESP32-S3 MCU/485_RX: IC3.2 (VOA); also elsewhere on the board
/gerarchico Sheet/ESP32-S3 MCU/485_TX: IC3.3 (VIB); also elsewhere on the board
/gerarchico Sheet/ESP32-S3 MCU/CAN_RX: IC2.2 (VOA); also elsewhere on the board
/gerarchico Sheet/ESP32-S3 MCU/CAN_TX: IC2.3 (VIB); also elsewhere on the board
/gerarchico Sheet/ESP32-S3 MCU/U0RXD: IC7.1 (TXD(O)); also elsewhere on the board
/gerarchico Sheet/ESP32-S3 MCU/U0TXD: IC7.4 (RXD(I)); also elsewhere on the board
/gerarchico Sheet/bus/485RXD_OPTO: IC3.7 (VIA), IC6.1 (RO)
/gerarchico Sheet/bus/485TXD_OPTO: IC3.6 (VOB), IC6.4 (DI)
/gerarchico Sheet/bus/A: C35.2, D10.1 (K1), FL2.4, R28.2, RS1.1
/gerarchico Sheet/bus/A_INT: FL2.1, IC6.6 (A), R22.1
/gerarchico Sheet/bus/B: C36.1, D10.2 (K2), FL2.3, R28.1, RS1.2
/gerarchico Sheet/bus/B_INT: FL2.2, IC6.7 (B), R23.2
/gerarchico Sheet/bus/CANH: C31.1, FL1.1, IC5.7 (CANH)
/gerarchico Sheet/bus/CANH_CONN: C33.1, CAN1.1, D9.2 (K2), FL1.4, R29.2
/gerarchico Sheet/bus/CANL: C31.2, FL1.2, IC5.6 (CANL)
/gerarchico Sheet/bus/CANL_CONN: C34.1, CAN1.2, D9.1 (K1), FL1.3, R29.1
/gerarchico Sheet/bus/CANRXD_OPTO: IC2.7 (VIA), IC5.4 (RXD(O))
/gerarchico Sheet/bus/CANTXD_OPTO: IC2.6 (VOB), IC5.1 (TXD(I))
/gerarchico Sheet/bus/USBIN1_N: IC4.3 (I/O2_1), J4.3, USBC_FTDI1.A7 (DN1), USBC_FTDI1.B7 (DN2)
/gerarchico Sheet/bus/USBIN1_P: IC4.1 (I/O1_1), J4.2, USBC_FTDI1.A6 (DP1), USBC_FTDI1.B6 (DP2)
/gerarchico Sheet/bus/USBOUT1_N: IC4.4 (I/O2_2), IC7.9 (USBDM)
/gerarchico Sheet/bus/USBOUT1_P: IC4.6 (I/O1_2), IC7.8 (USBDP)
/gerarchico Sheet/bus/VCCIO: C32.1, IC7.3 (VCCIO), IC7.10 (3V3OUT), IC7.11 (RESET#), R26.2, R27.2
GND: C22.2, C23.2, C24.2, C28.2, C32.2, IC2.4 (GND1), IC3.4 (GND1), IC4.2 (GND), IC7.5 (GND_1), IC7.13 (GND_2), J4.1, PS2.1 (-VIN_(GND)), R17.1, R18.1, R19.1, USBC_FTDI1.A1 (GND), USBC_FTDI1.A12 (GND), USBC_FTDI1.B1 (GND), USBC_FTDI1.B12 (GND); also elsewhere on the board
GNDISO: C25.2, C26.2, C27.2, C29.2, C30.2, C33.2, C34.2, C35.1, C36.2, CAN1.3, D9.3 (CC), D10.3 (CC), IC2.5 (GND2), IC3.5 (GND2), IC5.2 (VSS), IC6.5 (GND), PS2.3 (-VOUT), R21.2, R23.1, RS1.3
unnamed: C24.1, R19.2, USBC_FTDI1.SH2 (SHIELD)
unnamed: D7.2 (A), R26.1
unnamed: D7.1 (K), IC7.7 (CBUS2)
unnamed: D8.2 (A), R27.1
unnamed: D8.1 (K), IC7.14 (CBUS1)
unnamed: IC5.8 (STBY), R21.1
unnamed: IC6.2 (~RE), IC6.3 (~SHDN), R20.2
unnamed: R18.2, USBC_FTDI1.A5 (CC1)
unnamed: R17.2, USBC_FTDI1.B5 (CC2)

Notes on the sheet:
USB-UART
CAN-BUS
RS-485

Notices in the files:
README.md:
License and contact:
Reproducing this board for mass production or for commercial purposes is **not allowed**. For business proposals, write to info@pcbsemplice.com.
For questions, feedback or suggestions, write to info@pcbsemplice.com.
If you are interested in these projects and want to support the development of boards, open-source projects, prototypes and documentation, you can make a donation on [PayPal](https://shorturl.at/0LquK). Every contribution, however small, makes a difference. Thank you!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
